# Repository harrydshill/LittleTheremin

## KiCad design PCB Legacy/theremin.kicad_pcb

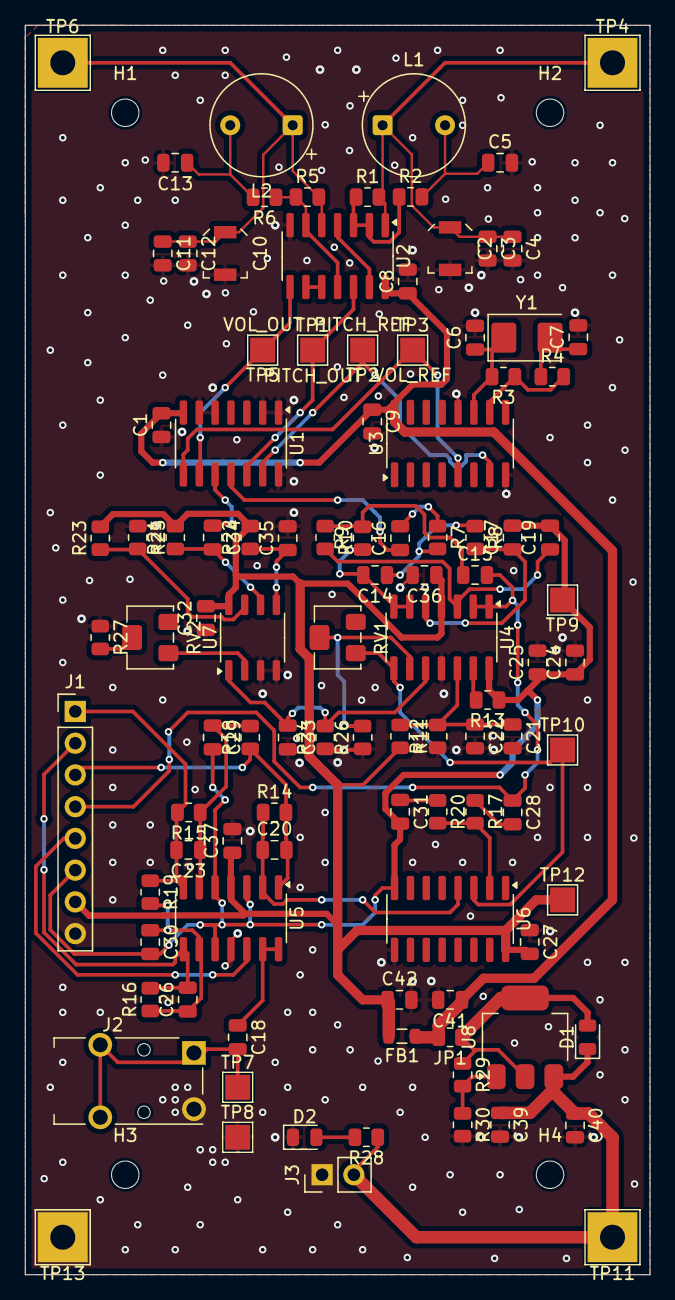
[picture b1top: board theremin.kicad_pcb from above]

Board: 2 copper layers, 50.0 x 100.0 mm, 108 parts (0 on the bottom side), 54 nets.

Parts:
C1, C8, C9, C16, C21, C24, C27, C32, C36, C37: 100n; C_0805_2012Metric
C2, C10: 0-80p; C_Trimmer_Voltronics_JR
C3, C11: 10p; C_0805_2012Metric
C4: 150p; C_0805_2012Metric
C5, C12: 220p; C_0805_2012Metric
C6, C7: 33p; C_0805_2012Metric
C13: 270p; C_0805_2012Metric
C14: 2.4n; C_0805_2012Metric
C15: 620p; C_0805_2012Metric
C17: 240p; C_0805_2012Metric
C18: 2.7u; C_0805_2012Metric
C19, C34: 470p; C_0805_2012Metric
C20: 100p; C_0805_2012Metric
C22, C25, C28: 10u; C_0805_2012Metric
C23, C26, C29, C30, C35: 10n; C_0805_2012Metric
C31: 1.2n; C_0805_2012Metric
C33, C39, C41, C42: 1u; C_0805_2012Metric
C40: 100u; C_0805_2012Metric
D1: 1N4002; D_0805_2012Metric
D2: RED; LED_0805_2012Metric
FB1: FerriteBead_Small; L_0805_2012Metric
H1, H2, H3, H4: MountingHole; MountingHole_2.2mm_M2
J1: Conn_01x08_Pin; PinHeader_1x08_P2.54mm_Vertical
J2: AudioJack3; Jack_3.5mm_Switronic_ST-005-G_horizontal
J3: PWR; PinHeader_1x02_P2.54mm_Vertical
JP1: Jumper_2_Open; R_0805_2012Metric
L1: 1m; CP_Radial_Tantal_D8.0mm_P5.00mm
L2: 3m; CP_Radial_Tantal_D8.0mm_P5.00mm
R1, R3, R5: 4.7M; R_0805_2012Metric
R2, R6, R11, R12, R15, R16, R18, R19, R21, R23, R29: 10k; R_0805_2012Metric
R4, R27: 2.2k; R_0805_2012Metric
R7: 27k; R_0805_2012Metric
R8, R10, R24: 100k; R_0805_2012Metric
R9: 51k; R_0805_2012Metric
R13: 5k; R_0805_2012Metric
R14, R17, R26: 20k; R_0805_2012Metric
R20: 220; R_0805_2012Metric
R22: 6.8k; R_0805_2012Metric
R25: 47k; R_0805_2012Metric
R28: 560; R_0805_2012Metric
R30: 1.2k; R_0805_2012Metric
RV1: 50k; Potentiometer_Bourns_3224W_Vertical
RV2: 5k; Potentiometer_Bourns_3224W_Vertical
TP1: PITCH_OUT; TestPoint_Pad_2.0x2.0mm
TP2: PITCH_REF; TestPoint_Pad_2.0x2.0mm
TP3: VOL_REF; TestPoint_Pad_2.0x2.0mm
TP4: PITCH; TestPoint_THTPad_4.0x4.0mm_Drill2.0mm
TP5: VOL_OUT; TestPoint_Pad_2.0x2.0mm
TP6: VOL; TestPoint_THTPad_4.0x4.0mm_Drill2.0mm
TP7: AUDIO; TestPoint_Pad_2.0x2.0mm
TP8: GND; TestPoint_Pad_2.0x2.0mm
TP9: ANA_REF; TestPoint_Pad_2.0x2.0mm
TP10: VOL_CV; TestPoint_Pad_2.0x2.0mm
TP11: V+; TestPoint_THTPad_4.0x4.0mm_Drill2.0mm
TP12: VDD_ANA; TestPoint_Pad_2.0x2.0mm
TP13: GND; TestPoint_THTPad_4.0x4.0mm_Drill2.0mm
U1: 4070; SOIC-14_3.9x8.7mm_P1.27mm
U2: 40106; SOIC-14_3.9x8.7mm_P1.27mm
U3: 4060B; SOP-16_3.9x9.9mm_P1.27mm
U4, U5: OPA1679; SOIC-14_3.9x8.7mm_P1.27mm
U6: SSI2164; SOIC-16_3.9x9.9mm_P1.27mm
U7: LM331N; SOP-8_3.9x4.9mm_P1.27mm
U8: LM317_SOT-223; SOT-223-3_TabPin2
Y1: 8MHz; Crystal_SMD_5032-2Pin_5.0x3.2mm

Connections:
/Oscillators/PITCH_MIXED: C16.1, U1.11
/Oscillators/PITCH_OUT: TP1.1, U1.12, U2.12
/Oscillators/VOL_MIXED: C34.1, U1.10
/Oscillators/VOL_OUT: TP5.1, U1.9, U2.8
/Signal Processing/PITCH_FILTERED: C15.2, C28.1, J1.4, U4.1, U4.2 (-)
/Signal Processing/SEL0: J1.5, U5.12 (+)
/Signal Processing/SINE_OUT: C20.2, J1.3, R14.2, R18.1, U5.1
/Signal Processing/SQUARE_OUT: C23.2, J1.1, R15.2, R19.1, U5.7
/Signal Processing/TRI_OUT: C26.2, J1.2, R16.2, U5.8
/Signal Processing/VOL_CV: RV1.1, TP10.1, U4.8, U6.3 (VC1)
ANA_REF: C17.2, C19.2, C24.1, C25.1, C29.2, C30.2, C31.2, J1.6, R13.1, TP9.1, U4.14, U5.3 (+), U5.5 (+), U5.10 (+), U6.8 (GND)
ANA_VDD: C27.2, C32.2, C36.1, C37.1, C42.1, FB1.2, J1.7, R11.2, R21.2, R22.2, R23.2, TP12.1, U4.4 (V+), U5.4 (V+), U6.16 (V+), U7.8 (VS)
GND: C1.1, C2.2, C3.2, C4.2, C5.2, C6.2, C7.2, C8.2, C9.2, C10.2, C11.2, C12.2, C13.2, C21.2, C22.2, C24.2, C25.2, C27.1, C32.1, C33.2, C35.2, C36.2, C37.2, C39.2, C40.2, C41.2, C42.2, D2.1 (K), J1.8, J2.S, J3.1, R12.1, R24.1, R25.1, R26.1, R27.1, R30.2, TP8.1, TP13.1, U1.1, U1.2, U1.5, U1.6, U1.14 (VDD), U2.7 (VSS), U3.8 (VSS), U3.12 (CLR), U4.11 (V-), U5.11 (V-), U6.9 (V-), U7.3 (FOUT), U7.4 (GND)
unnamed: C2.1, C3.1, C4.1, L1.1, R1.2, TP4.1, U2.1
unnamed: C5.1, L1.2, R2.2
unnamed: C7.1, R4.1, Y1.2
unnamed: C10.1, C11.1, C12.1, L2.1, R5.2, TP6.1, U2.5
unnamed: C13.1, L2.2, R6.2
unnamed: C14.1, R7.2, R8.1
unnamed: C15.1, R9.2, R10.1
unnamed: C16.2, R7.1
unnamed: C18.2, J2.R, J2.T, TP7.1
unnamed: C28.2, R17.1
unnamed: C31.1, R20.1
unnamed: D1.2 (A), JP1.1 (A), R29.1, U8.2 (VO)
unnamed: C39.1, C40.1, D1.1 (K), J3.2, R28.1, TP11.1, U8.3 (VI)
unnamed: D2.2 (A), R28.2
unnamed: R1.1, R2.1, U2.2, U2.3
unnamed: R5.1, R6.1, U2.6, U2.11
unnamed: R27.2, RV2.2
unnamed: U2.9, U2.10
unnamed: U2.4, U2.13
unnamed: TP2.1, U1.13, U3.7 (Q4)
unnamed: TP3.1, U1.8, U3.5 (Q5)
unnamed: C6.1, R3.2, U3.11 (~Φ1), Y1.1
unnamed: R3.1, R4.2, U3.10 (Φ0)
unnamed: C19.1, R10.2, U4.3 (+)
unnamed: C17.1, R8.2, U4.5 (+)
unnamed: C14.2, R9.1, U4.6 (-), U4.7
unnamed: C33.1, R24.2, U4.10 (+), U7.1 (IOUT)
unnamed: R26.2, RV1.2, U4.9 (-)
unnamed: C21.1, C22.1, R11.1, R12.2, U4.12 (+)
unnamed: R13.2, U4.13 (-)
unnamed: C20.1, R14.1, U5.2 (-), U6.4 (I_OUT1)
unnamed: C23.1, C29.1, R15.1, R18.2, U5.6 (-)
unnamed: C26.1, C30.1, R16.1, R19.2, U5.9 (-)
unnamed: C18.1, U5.13 (-), U5.14
unnamed: R17.2, R20.2, U6.2 (I_IN1)
unnamed: R23.1, R25.2, U7.7 (COMPIN)
unnamed: RV2.1, U7.2 (IREF)
unnamed: C35.1, R22.1, U7.5 (RC)
unnamed: C34.2, R21.1, U7.6 (THRESH)
unnamed: R29.2, R30.1, U8.1 (ADJ)
VDD: C1.2, C8.1, C9.1, C41.1, FB1.1, JP1.2 (B), U1.7 (VSS), U2.14 (VDD), U3.16 (VDD)

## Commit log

2026-04-19 current work
2026-04-19 block diagram and file rearrangement
2026-05-10 sims
2026-05-16 minor
2026-05-19 ijnt
2026-05-19 forgot to push the new theremin duh
